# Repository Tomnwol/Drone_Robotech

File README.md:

Bienvenue dans le git du drone de **Robotech** 2025/2026.
Notre projet est de créer un drone 5" basé sur une ESP32.

# -- Démarche globale --

L'idée principale est d'utiliser un IMU 9 axes (accéléromètre, gyroscope, magnétomètre) pour obtenir une estimation d'attitude et ainsi pouvoir obtenir une commande angulaire qui sera par la suite exécutée par les moteurs.

# -- COMPOSANTS --

- Microprocesseur : *ESP32 DevKit*
- Accéléromètre/Gyroscope : *MPU-9265*
- Magnétomètre : *GY-271* (optionnel)
- Moteurs : *XING-E Pro 2207 1800KV 2-6S - Iflight*
- ESC : Hobbywing - *XRotor Micro 65A G2 4in1 AM32*
- Batterie : *LiPo GNB 6S 2200mAh 120C - XT60 - Gaoneng*
- Antenne RF : *NRF24L01 + PA/LNA*
- Frame : créée sur Fusion et imprimée en 3D
- PCB : créé sur Kicad 9

# -- CODE --

Pour le code, après avoir eu des problèmes de librairie en ESP-IDF sur **PlatformIo** pour le DSHOT, nous avons finalement migré vers **Arduino IDE** pour avoir une version plus récente de la librairie DSHOTRMT.

# -- SIMULATION --

Un fichier de simulation est disponible dans le répertoire /Simulation et permet de visualiser si le calcul d'attitude est cohérent et de visualiser 4 réponses moteurs, permettant ainsi de modifier les PID en conséquence.

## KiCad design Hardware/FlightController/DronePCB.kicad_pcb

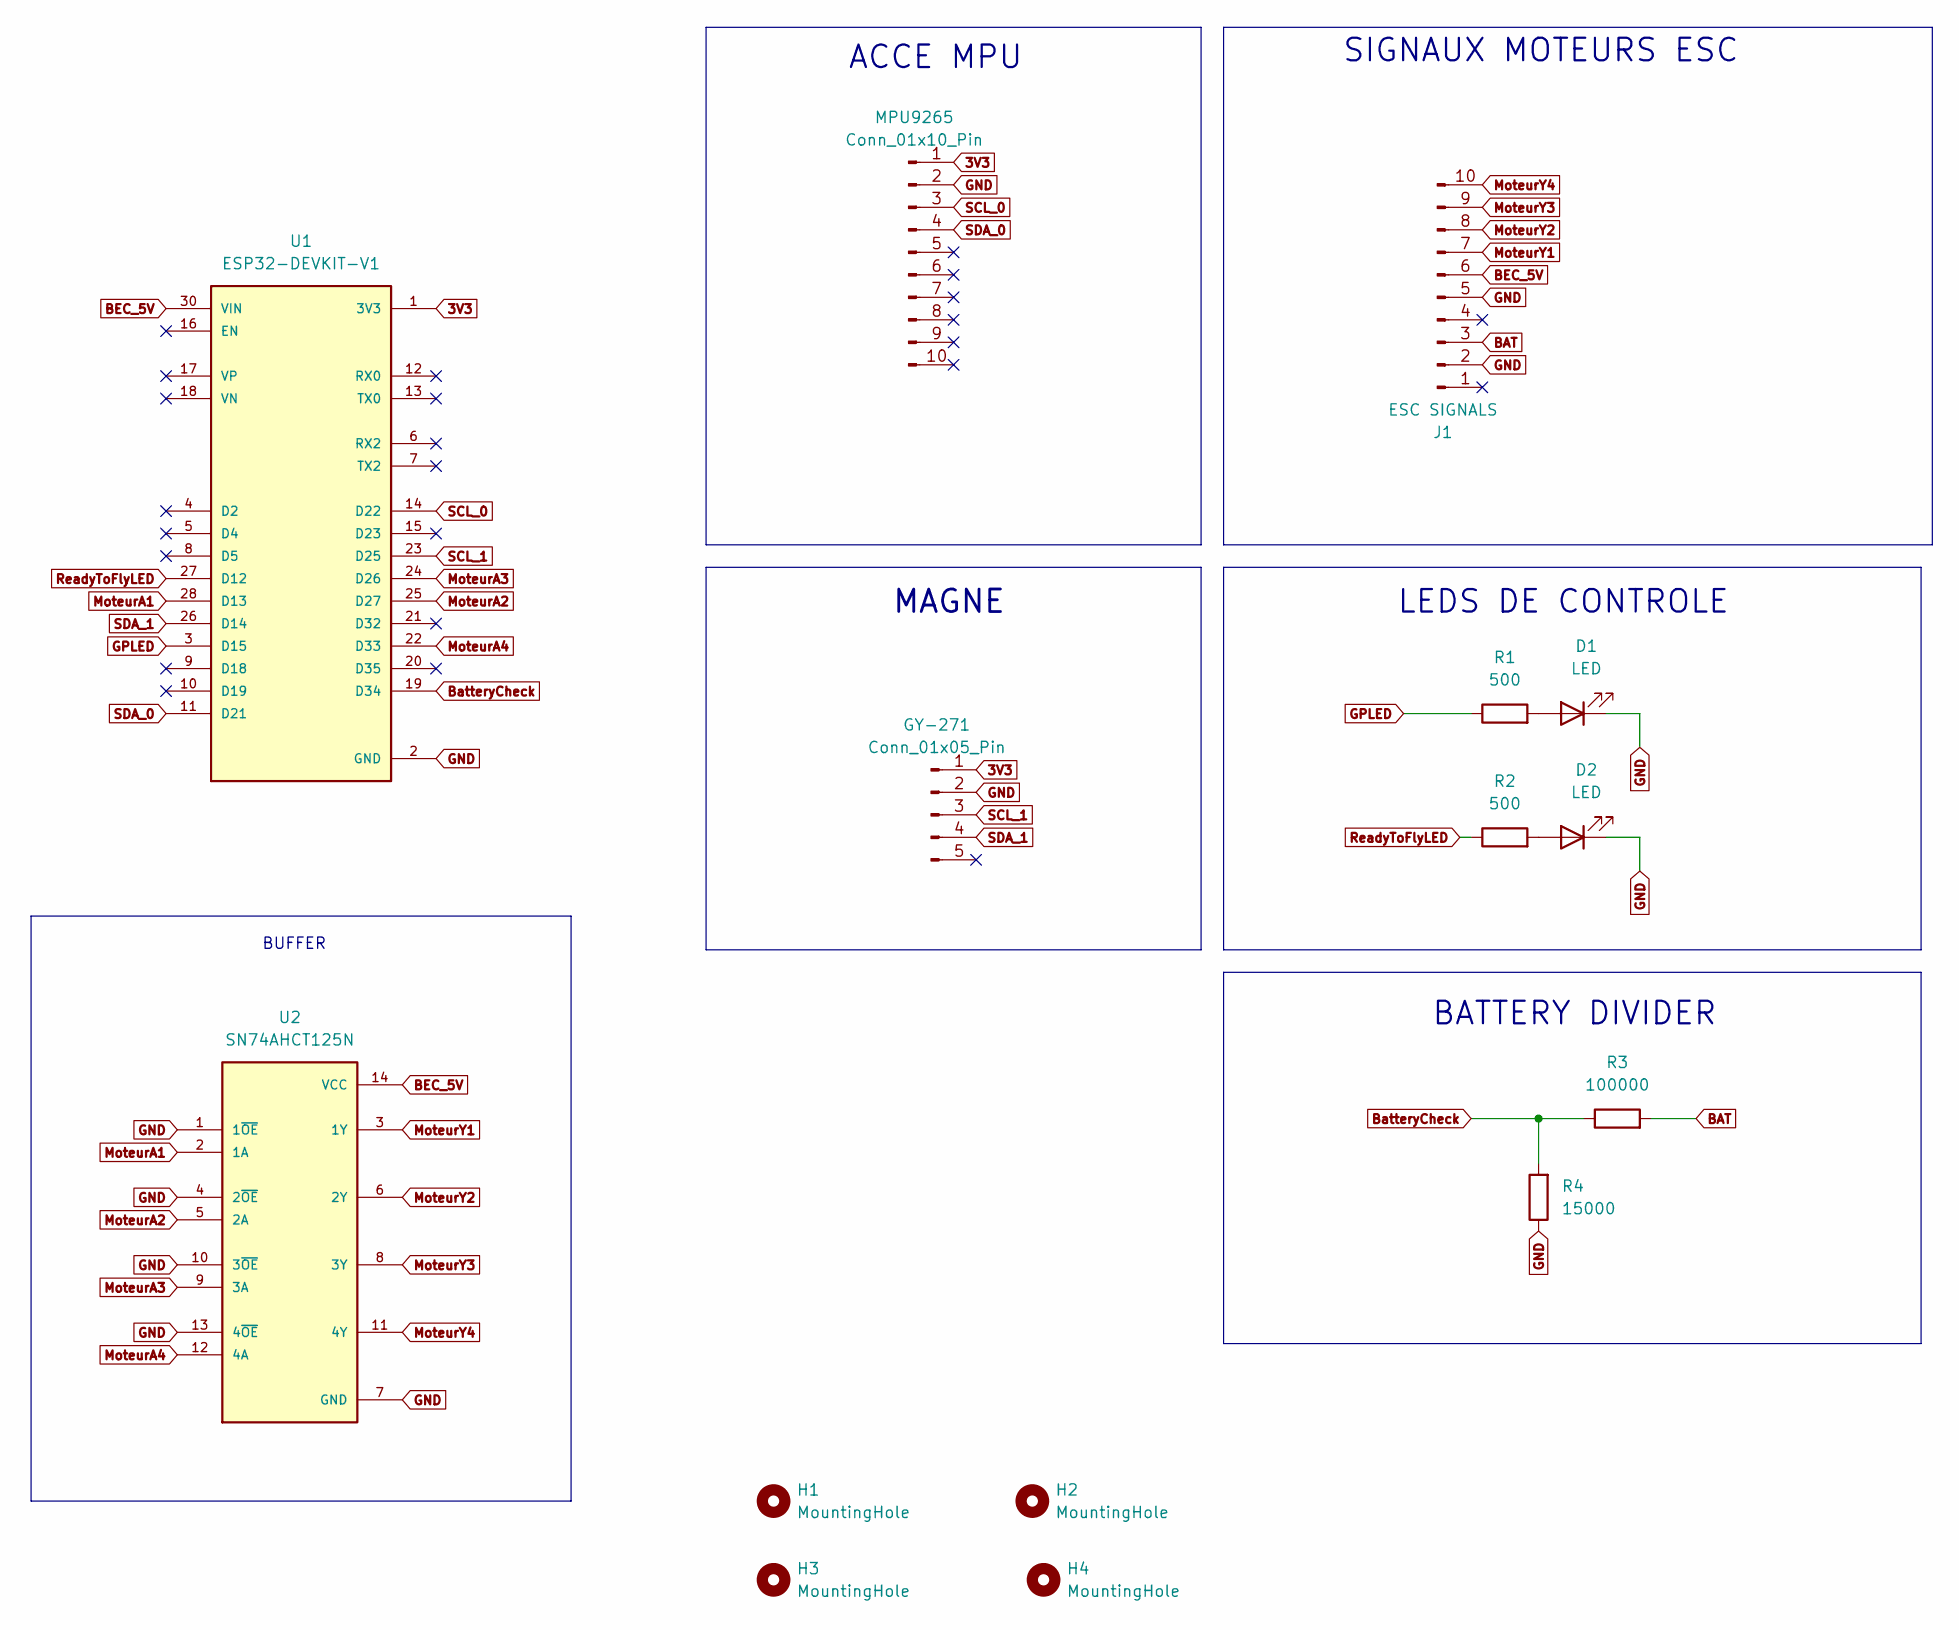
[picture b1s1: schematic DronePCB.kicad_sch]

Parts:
D1, D2: LED; LED_0603_1608Metric_Pad1.05x0.95mm_HandSolder
GY-271: Conn_01x05_Pin; PinHeader_1x05_P2.54mm_Vertical
H1, H2, H3, H4: MountingHole; MountingHole_3.2mm_M3_Pad
J1: ESC SIGNALS; JST_SHL_SM10B-SHLS-TF_1x10-1MP_P1.00mm_Horizontal
MPU9265: Conn_01x10_Pin; PinHeader_1x10_P2.54mm_Vertical
R1, R2: 500; R_0603_1608Metric_Pad0.98x0.95mm_HandSolder
R3: 100000; R_0603_1608Metric_Pad0.98x0.95mm_HandSolder
R4: 15000; R_0603_1608Metric_Pad0.98x0.95mm_HandSolder
U1: ESP32-DEVKIT-V1; MODULE_ESP32_DEVKIT_V1; PARTREV N/A
U2: SN74AHCT125N; DIP794W45P254L1930H508Q14; PARTREV Q

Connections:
3V3: GY-271.1, MPU9265.1, U1.1 (3V3)
BAT: J1.3, R3.2
BEC_5V: J1.6, U1.30 (VIN), U2.14 (VCC)
BatteryCheck: R3.1, R4.2, U1.19 (D34)
GND: D1.1 (K), D2.1 (K), GY-271.2, J1.2, J1.5, MPU9265.2, R4.1, U1.2 (GND), U1.29 (GND), U2.1 (1~OE), U2.4 (2~OE), U2.7 (GND), U2.10 (3~OE), U2.13 (4~OE)
GPLED: R1.1, U1.3 (D15)
MoteurA1: U1.28 (D13), U2.2 (1A)
MoteurA2: U1.25 (D27), U2.5 (2A)
MoteurA3: U1.24 (D26), U2.9 (3A)
MoteurA4: U1.22 (D33), U2.12 (4A)
MoteurY1: J1.7, U2.3 (1Y)
MoteurY2: J1.8, U2.6 (2Y)
MoteurY3: J1.9, U2.8 (3Y)
MoteurY4: J1.10, U2.11 (4Y)
unnamed: D1.2 (A), R1.2
unnamed: D2.2 (A), R2.2
ReadyToFlyLED: R2.1, U1.27 (D12)
SCL_0: MPU9265.3, U1.14 (D22)
SCL_1: GY-271.3, U1.23 (D25)
SDA_0: MPU9265.4, U1.11 (D21)
SDA_1: GY-271.4, U1.26 (D14)

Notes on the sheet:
ACCE MPU
MAGNE
BUFFER
BATTERY DIVIDER
LEDS DE CONTROLE
SIGNAUX MOTEURS ESC

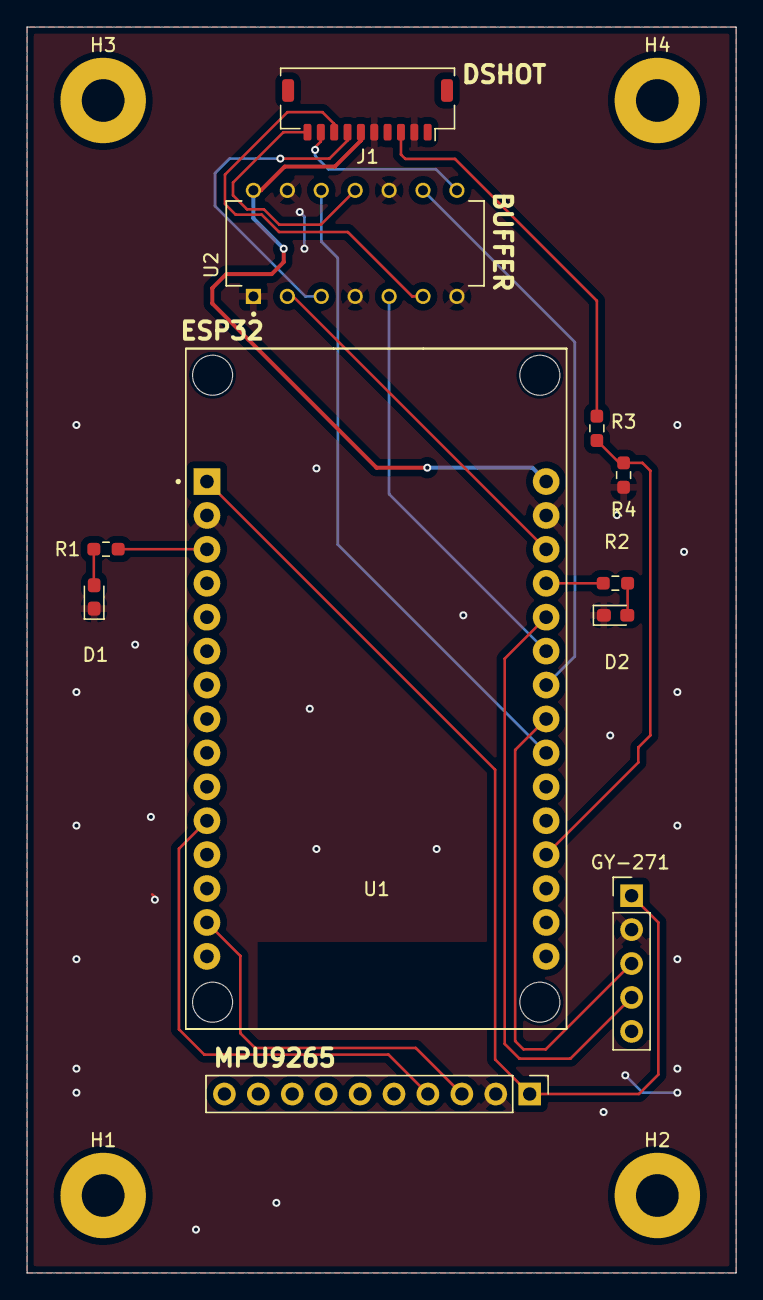
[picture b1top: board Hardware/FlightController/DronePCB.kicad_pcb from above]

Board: 2 copper layers, 53.1 x 93.3 mm, 15 parts (0 on the bottom side), 21 nets.

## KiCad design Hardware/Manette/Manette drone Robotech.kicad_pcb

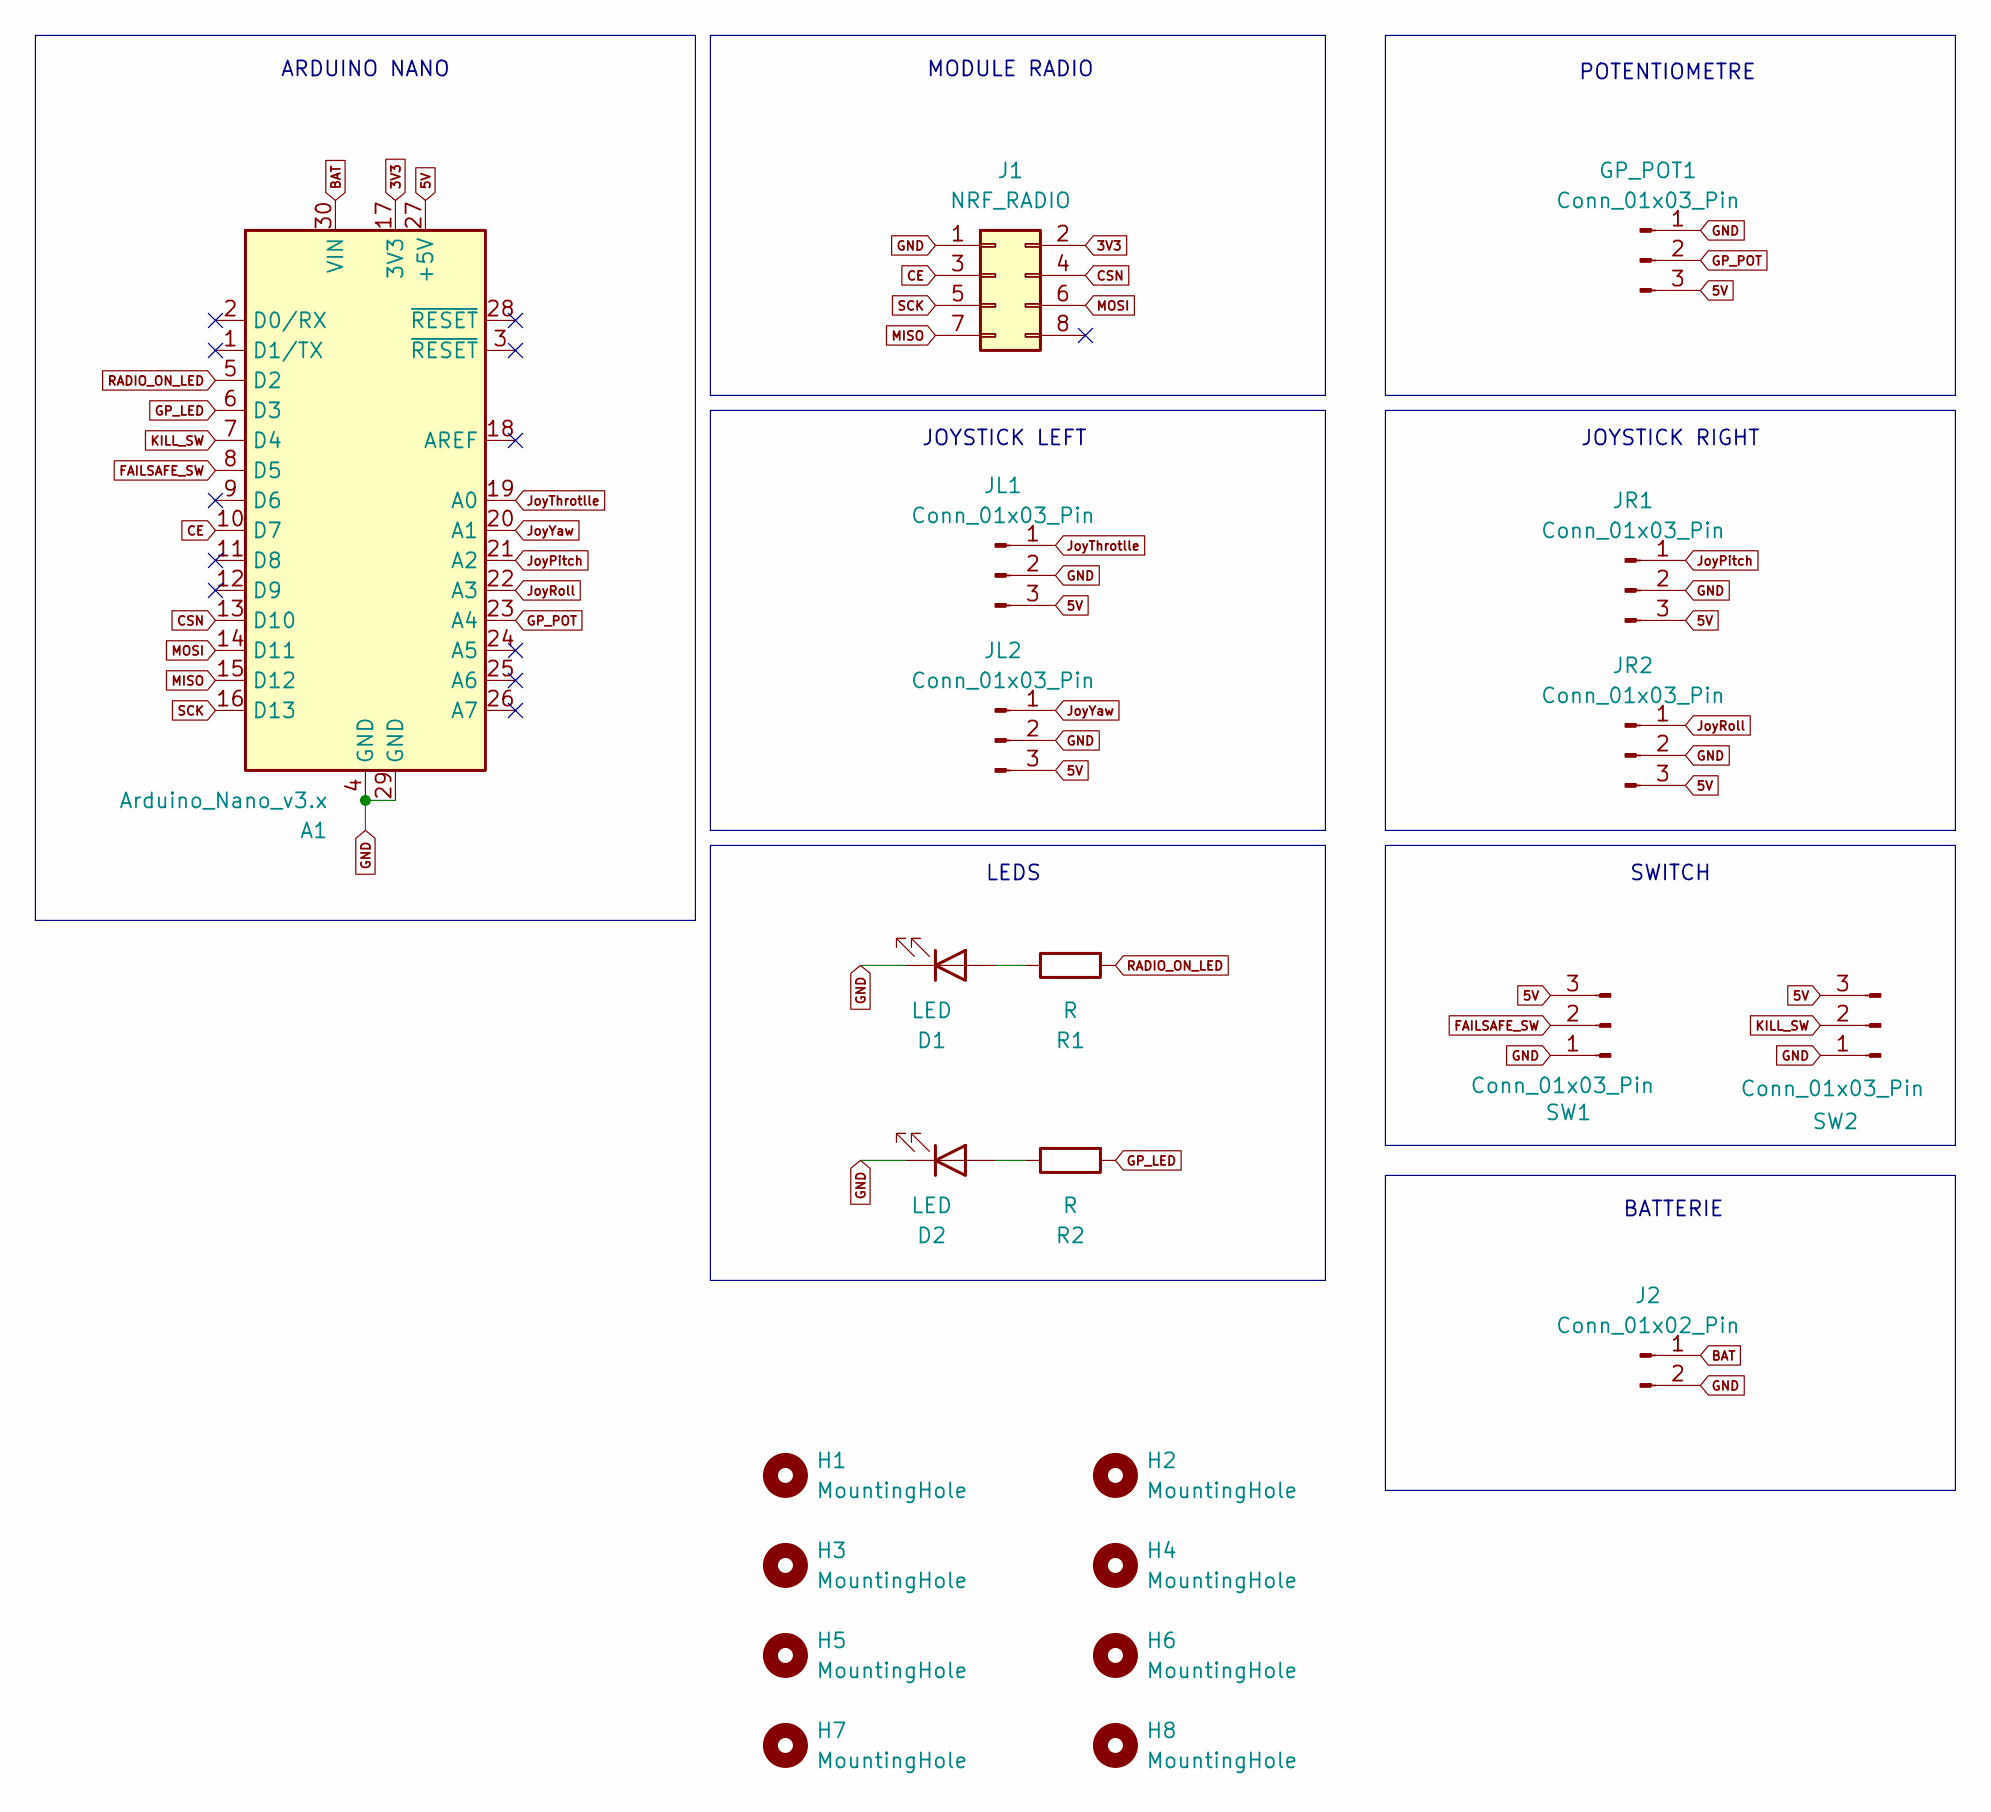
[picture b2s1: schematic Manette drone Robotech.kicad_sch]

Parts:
A1: Arduino_Nano_v3.x; Arduino_Nano
D1, D2: LED; LED_0603_1608Metric_Pad1.05x0.95mm_HandSolder
GP_POT1: Conn_01x03_Pin; PinHeader_1x03_P2.54mm_Vertical
H1, H2, H3, H4, H5, H6, H7, H8: MountingHole; MountingHole_3.2mm_M3_Pad
J1: NRF_RADIO; PinHeader_2x04_P2.54mm_Vertical
J2: Conn_01x02_Pin; PinHeader_1x02_P2.54mm_Vertical
JL1, JL2: Conn_01x03_Pin; PinHeader_1x03_P2.54mm_Vertical
JR1, JR2: Conn_01x03_Pin; PinHeader_1x03_P2.54mm_Vertical
R1, R2: R; R_0603_1608Metric_Pad0.98x0.95mm_HandSolder
SW1, SW2: Conn_01x03_Pin; PinHeader_1x03_P2.54mm_Vertical

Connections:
3V3: A1.17 (3V3), J1.2
5V: A1.27 (+5V), GP_POT1.3, JL1.3, JL2.3, JR1.3, JR2.3, SW1.3, SW2.3
BAT: A1.30 (VIN), J2.1
CE: A1.10 (D7), J1.3
CSN: A1.13 (D10), J1.4
FAILSAFE_SW: A1.8 (D5), SW1.2
GND: A1.4 (GND), A1.29 (GND), D1.1 (K), D2.1 (K), GP_POT1.1, J1.1, J2.2, JL1.2, JL2.2, JR1.2, JR2.2, SW1.1, SW2.1
GP_LED: A1.6 (D3), R2.2
GP_POT: A1.23 (A4), GP_POT1.2
JoyPitch: A1.21 (A2), JR1.1
JoyRoll: A1.22 (A3), JR2.1
JoyThrotlle: A1.19 (A0), JL1.1
JoyYaw: A1.20 (A1), JL2.1
KILL_SW: A1.7 (D4), SW2.2
MISO: A1.15 (D12), J1.7
MOSI: A1.14 (D11), J1.6
unnamed: D1.2 (A), R1.1
unnamed: D2.2 (A), R2.1
RADIO_ON_LED: A1.5 (D2), R1.2
SCK: A1.16 (D13), J1.5

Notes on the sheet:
JOYSTICK LEFT
JOYSTICK RIGHT
MODULE RADIO
SWITCH
LEDS
BATTERIE
POTENTIOMETRE
ARDUINO NANO

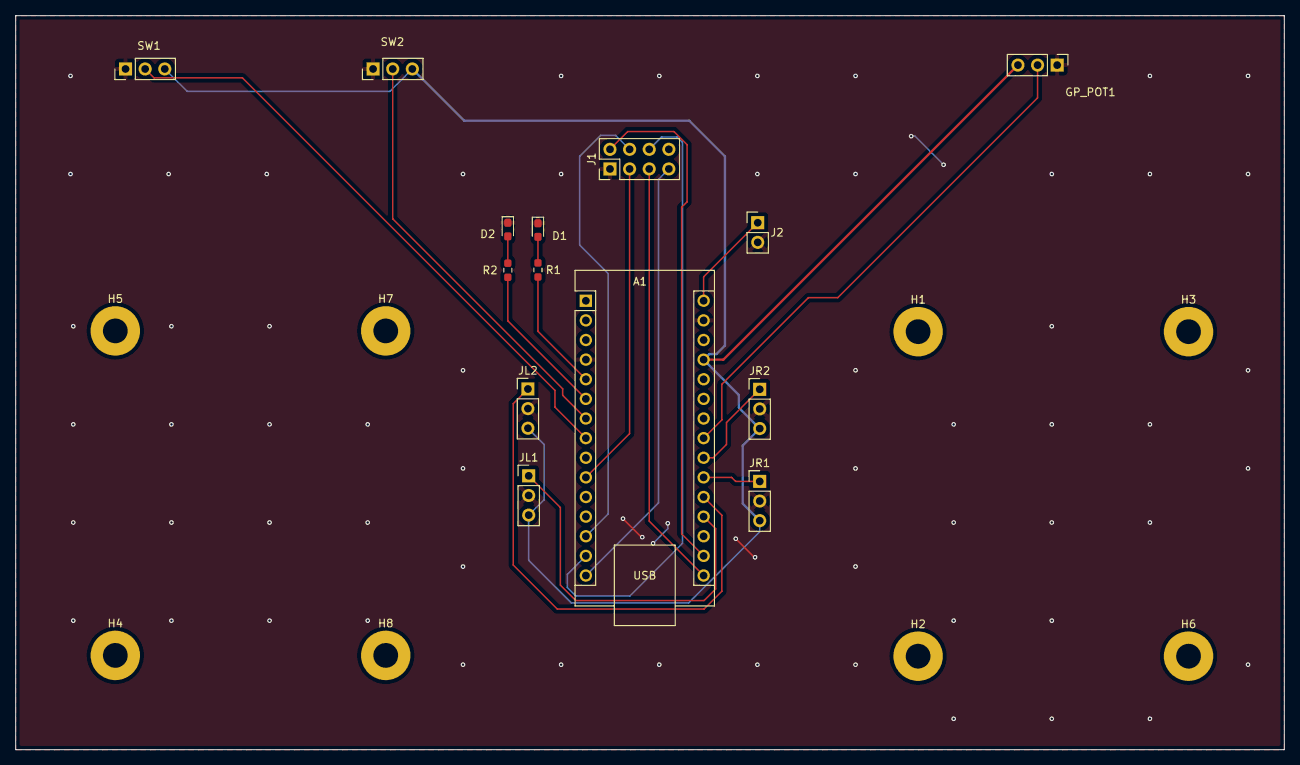
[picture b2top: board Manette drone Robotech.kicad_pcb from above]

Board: 2 copper layers, 164.2 x 95.0 mm, 22 parts (0 on the bottom side), 20 nets.

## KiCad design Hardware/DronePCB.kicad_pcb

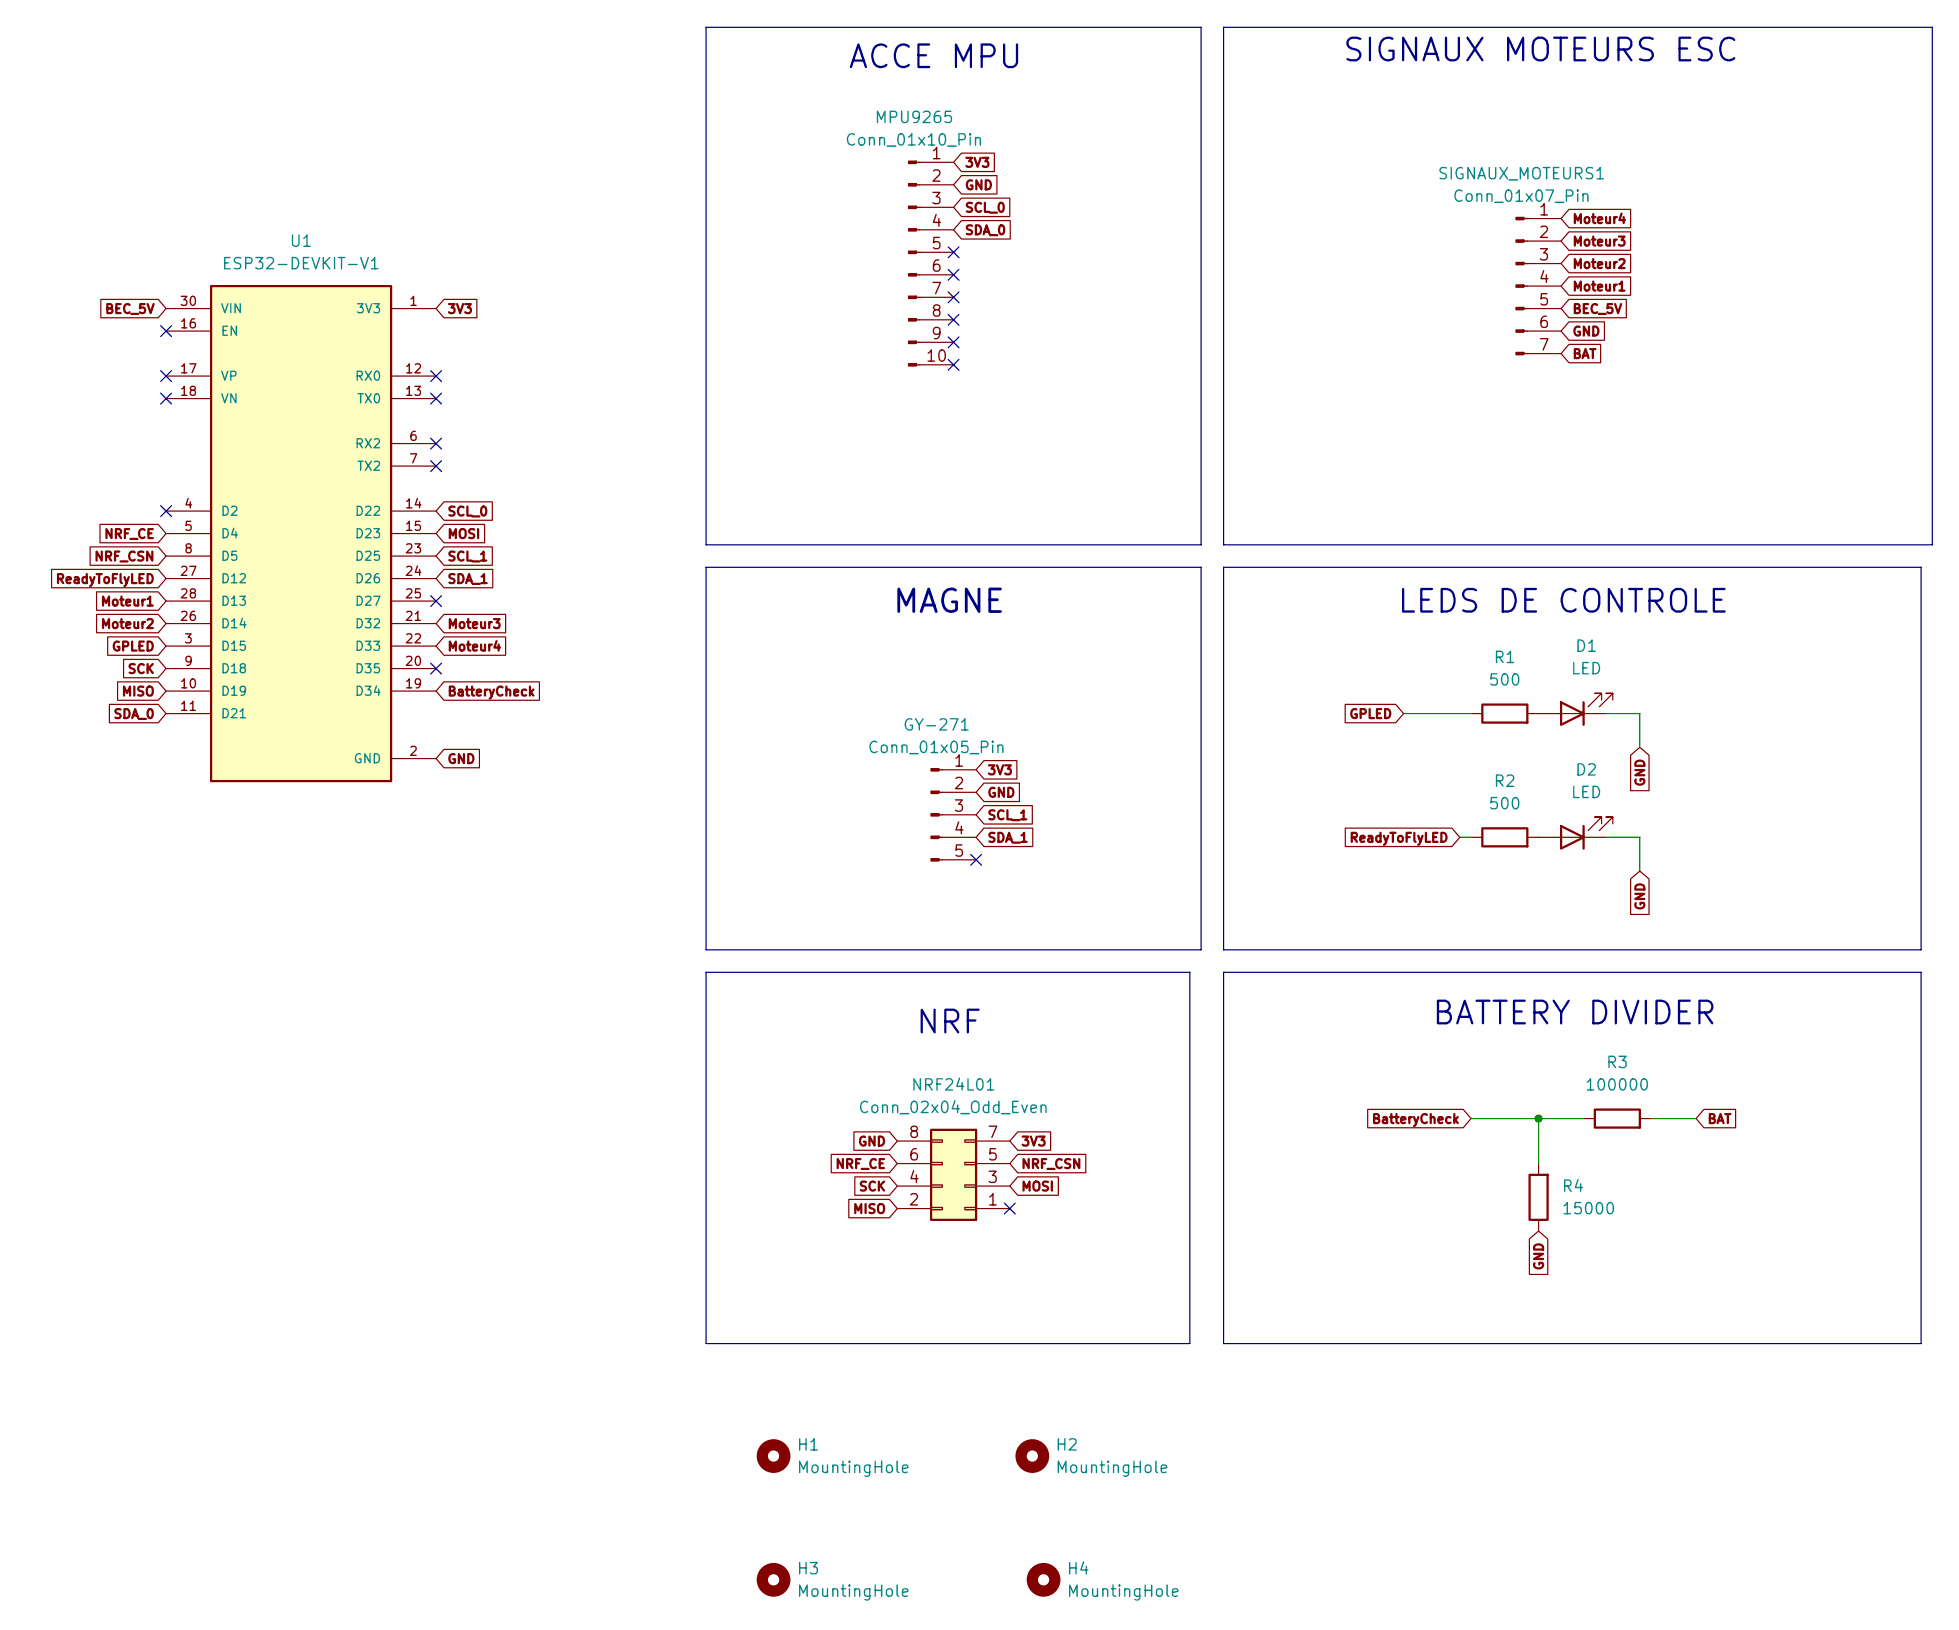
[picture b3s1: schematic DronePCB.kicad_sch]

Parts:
D1, D2: LED; LED_0603_1608Metric_Pad1.05x0.95mm_HandSolder
GY-271: Conn_01x05_Pin; PinHeader_1x05_P2.54mm_Vertical
H1, H2, H3, H4: MountingHole; MountingHole_3.2mm_M3_Pad
MPU9265: Conn_01x10_Pin; PinHeader_1x10_P2.54mm_Vertical
NRF24L01: Conn_02x04_Odd_Even; PinHeader_2x04_P2.00mm_Vertical
R1, R2: 500; R_0603_1608Metric_Pad0.98x0.95mm_HandSolder
R3: 100000; R_0603_1608Metric_Pad0.98x0.95mm_HandSolder
R4: 15000; R_0603_1608Metric_Pad0.98x0.95mm_HandSolder
SIGNAUX_MOTEURS1: Conn_01x07_Pin; PinHeader_1x07_P2.54mm_Vertical
U1: ESP32-DEVKIT-V1; MODULE_ESP32_DEVKIT_V1; PARTREV N/A

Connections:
3V3: GY-271.1, MPU9265.1, NRF24L01.7, U1.1 (3V3)
BAT: R3.2, SIGNAUX_MOTEURS1.7; also elsewhere on the board
BEC_5V: SIGNAUX_MOTEURS1.5, U1.30 (VIN); also elsewhere on the board
BatteryCheck: R3.1, R4.2, U1.19 (D34)
GND: D1.1 (K), D2.1 (K), GY-271.2, MPU9265.2, NRF24L01.8, R4.1, SIGNAUX_MOTEURS1.6, U1.2 (GND), U1.29 (GND); also elsewhere on the board
GPLED: R1.1, U1.3 (D15)
MISO: NRF24L01.2, U1.10 (D19)
MOSI: NRF24L01.3, U1.15 (D23)
Moteur1: SIGNAUX_MOTEURS1.4, U1.28 (D13); also elsewhere on the board
Moteur2: SIGNAUX_MOTEURS1.3, U1.26 (D14); also elsewhere on the board
Moteur3: SIGNAUX_MOTEURS1.2, U1.21 (D32); also elsewhere on the board
Moteur4: SIGNAUX_MOTEURS1.1, U1.22 (D33); also elsewhere on the board
NRF_CE: NRF24L01.6, U1.5 (D4)
NRF_CSN: NRF24L01.5, U1.8 (D5)
unnamed: D1.2 (A), R1.2
unnamed: D2.2 (A), R2.2
ReadyToFlyLED: R2.1, U1.27 (D12)
SCK: NRF24L01.4, U1.9 (D18)
SCL_0: MPU9265.3, U1.14 (D22)
SCL_1: GY-271.3, U1.23 (D25)
SDA_0: MPU9265.4, U1.11 (D21)
SDA_1: GY-271.4, U1.24 (D26)

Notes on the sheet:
ACCE MPU
MAGNE
BATTERY DIVIDER
LEDS DE CONTROLE
SIGNAUX MOTEURS ESC
NRF

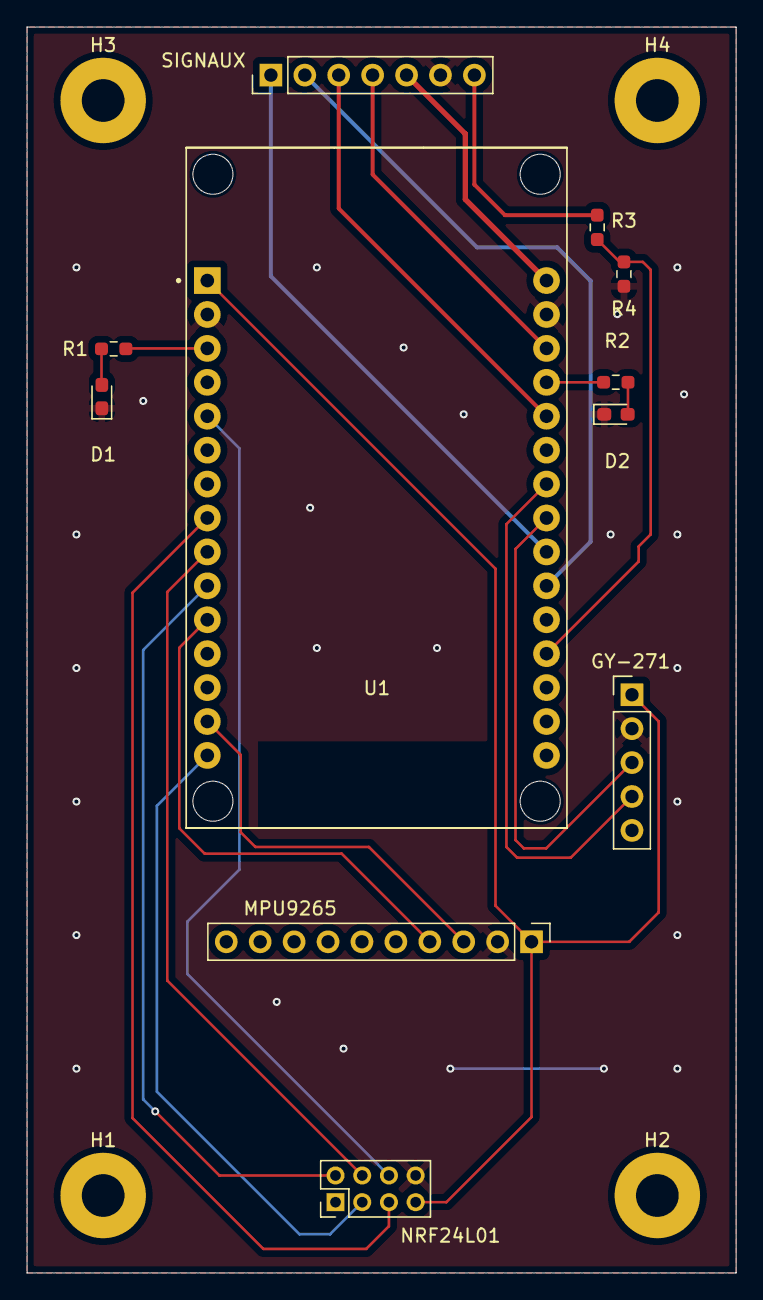
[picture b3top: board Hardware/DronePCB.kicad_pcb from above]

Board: 2 copper layers, 53.1 x 93.3 mm, 15 parts (0 on the bottom side), 22 nets.

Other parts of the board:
SIGNAUX: Conn_01x07_Pin; PinHeader_1x07_P2.54mm_Vertical

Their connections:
BAT: SIGNAUX.7; also elsewhere on the board
BEC_5V: SIGNAUX.5; also elsewhere on the board
GND: SIGNAUX.6; also elsewhere on the board
Moteur1: SIGNAUX.4; also elsewhere on the board
Moteur2: SIGNAUX.3; also elsewhere on the board
Moteur3: SIGNAUX.2; also elsewhere on the board
Moteur4: SIGNAUX.1; also elsewhere on the board

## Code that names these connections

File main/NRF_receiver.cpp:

#include <SPI.h>
#include <RF24.h>
#include "NRF_receiver.hpp"
// Définition des pins SPI pour ESP32
#define CE_PIN   4
#define CSN_PIN  5

//Pin non précisés : 
//SCK -> 18
//MISO -> 19
//MOSI -> 23
// Création de l'objet RF24
RF24 radio(CE_PIN, CSN_PIN);
// Adresse du pipe d'émission de l'Arduino
const byte pipeAddress[5] = {'P','I','P','E','1'};

#define PAYLOAD_SIZE 32
char payload[PAYLOAD_SIZE];

unsigned long radio_delta_time = 0; /*Sert à activer le Failsafe mode en cas de non-communication prolongée*/
unsigned long radio_last_time = 0;

uint16_t joyThrottle = 10; //Armer le drone  
uint16_t joyYaw = 0;
uint16_t joyRoll = 0;
uint16_t joyPitch = 0;
uint16_t GP_Pot = 0;
uint8_t SWFailSafe = 0;
uint8_t SWKillSwitch = 0;
float QT_KP = 0;
float QT_KI = 0;
float QT_KD = 0;
uint8_t offsetMotorFL = 0;
uint8_t offsetMotorFR = 0;
uint8_t offsetMotorBL = 0;
uint8_t offsetMotorBR = 0;
void setupNRF() {
  if (!radio.begin()) {
    Serial.println("Erreur: NRF24 non détecté !"); // else : allumer une led idéalement
    while (1);
    return;
  }
  // Paramètres identiques à l'émetteur
  radio.setAutoAck(false);   // DÉSACTIVE LES ACK
  radio.setRetries(0, 0);    // ⬅️ aucune tentative de retry
  radio.setChannel(0);              // Même canal que l'Arduino
  radio.setPALevel(RF24_PA_LOW);    // Même puissance
  radio.setDataRate(RF24_1MBPS);    // Même débit
  radio.openReadingPipe(0, pipeAddress); // Même adresse que l'émetteur
  radio.startListening();           // On passe en mode réception

  //Serial.println("NRF24 prêt à recevoir !");
  radio_last_time = millis();
}


void readNRFData() {
  radio_delta_time = millis() - radio_last_time;
  if (radio.available()) {
    radio.read(&payload, PAYLOAD_SIZE);  // Lecture du message
    if(payload[0] != NULL){
      radio_last_time = millis();
      //Serial.print("Message reçu: ");
      joyThrottle = payload[0] + (payload[1]<<8);
      joyYaw = payload[2] + (payload[3]<<8);
      joyRoll = payload[4] + (payload[5]<<8);
      joyPitch = payload[6] + (payload[7]<<8);
      GP_Pot = payload[8] + (payload[9]<<8);
      SWFailSafe = payload[10];
      SWKillSwitch = payload[11];
      QT_KP = ((float)(uint16_t)(payload[12] + (payload[13]<<8))/100.0); // Récupération du KP et KI, en pensant bien à diviser 100 pour retrouver les 2 décimales
      QT_KI = ((float)(uint16_t)(payload[14] + (payload[15]<<8))/100.0);
      QT_KD = ((float)(uint16_t)(payload[16] + (payload[17]<<8))/100.0);
      offsetMotorFL = payload[18];
      offsetMotorFR = payload[19];
      offsetMotorBL = payload[20];
      offsetMotorBR = payload[21];
    }
    //Serial.print("Throttle : ");
    //Serial.println(joyThrottle);
  }
}

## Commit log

2025-10-12 Add project sources
2025-10-12 3D display folder added
2025-10-12 files reorganization
2025-10-15 Seance 15_10 simplification code
2025-10-16 Hard iron magnetometer correction
2025-10-23 PWM motors simu v1
2025-11-02 utils file
2025-11-05 Update avant changement 2 coeurs utilisés
2025-11-09 Portage FrameWork ESP IDF to Arduino
2025-11-09 ajout slider moteur simulation
2025-11-10 Ajout script arduino pour telecommande
2025-11-10 Correction via yaw roll pitch fonctionnel
2025-11-12 Ajout code moteur | Non testé
2025-11-16 Réécriture du projet
2025-11-16 Add git ignore
2025-11-16 Kicad drone PCB
2025-11-16 add *readme
2025-11-16 Remove old folder after rename
2025-11-16 Rename README.txt to README.md
2025-12-03 Added Kicad for drone Remote Controller
2025-12-04 PCB Drone et manette finis avec gerbers générés
2025-12-04 mise a jour de tous les fichiers git
2025-12-05 Fix conversion issue on payload
2025-12-05 NRF variables def
2025-12-05 pid file
2025-12-05 KillSwitch delta radio a 5000 pour tester les reactions moteurs
2025-12-06 Correction Drone pinout et génération gerber
2025-12-08 qqs tests moteurs
2025-12-10 gerbers et code fonctionnel cut a 45°
2026-01-10 Code recoit infos manette, gere le throttle, et gestion du killswitch OK. Cependant, PB de GPIO qui se détruisent, probablement pic de courant ou tension
2026-01-30 QT Interface added
2026-01-31 Serial config QT interface
2026-01-31 Add controller code (without serial read)
2026-01-31 QT interface amélioration UI
2026-02-01 Update Drone, Controller and QT interface for KI and KP new integration
2026-02-02 Correction erreur controller
2026-02-07 PID Kd and motors offsets added
2026-02-09 controller debug change
2026-02-09 PID security update with I begin value
2026-02-09 security Killswitch added with no radio signal
2026-02-11 Communication by UDP to avoid NRF24L01 bugs
2026-02-11 QT new config systems
2026-02-12 MAJOR DEBUG BR BL INVERSION git add .! warning
2026-02-14 VERSION FONCTIONNEL DRONE, VOL DANS LE FAB
2026-02-14 Sauvegarde des offsets moteurs QT Interface
2026-02-14 Changement pas du PID slider QT interface
2026-02-14 Refacto ConfigBox
2026-02-15 Refacto avec main propre, boxs dans fichiers séparés
2026-02-15 Ajout Drone Box for battery data
2026-02-16 QT Interface for battery
2026-02-16 TEST pour télémétrie
2026-02-16 Version qui compile du test batterie
2026-02-16 fix battery pin
2026-02-25 PCB avec nouveau connecteur JST SH + buffer
2026-02-25 Critique : Inclusion de ROLL et PITCH dans le drone, code QT pour roll pitch egalement
2026-02-25 Drone code fix (see last commit)
2026-02-28 Add drone's datas on QT interface
2026-03-01 Interface QT accepte désormais manette Nacon revolution X
2026-03-01 Qqs corrections et stylessheets
2026-03-01 Throttle par dérivée et non pas valeur brute
2026-03-08 Connexion wifi via checkBox
2026-03-09 Debug startBox signals
2026-03-09 QT styles file for lisibility
2026-03-12 CRITICAL FIX! Cause : function with no return | Consequences : Illegal instruction/ESP reboot
2026-03-12 Debug WIP motors telemetry
2026-03-12 Inversion axis +pitch and -pitch & Inversion axis roll+ and roll- in QT controller. Delete some ESP debugs displays and limit failsafe value to 800
2026-03-13 Yaw integration in drone code | Non-tested feature
2026-03-13 QT Wifi connection UI UX update | Try to debug KS issue
2026-03-13 debug..
2026-03-13 debug...
2026-03-13 Communication Bug fixed by use of threads for network manager QT calls
2026-03-16 Resize limits on K_pid on QT
2026-03-17 Add PID edit by controller + UI WIP
2026-03-18 New UI
2026-03-18 Debug du moteur qui ne tournait pas par suppression d'un delay + init UDP plus tot
2026-03-18 Rework throttle curve in QT
2026-03-19 yaw on throttle joystick + font resize
2026-04-02 yaw inverted issue
2026-04-02 offsets accelerometer fix
